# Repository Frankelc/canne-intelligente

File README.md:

# IFRI · Certification SEIoT · Projet 3

## Canne et lunettes intelligentes pour personnes non voyantes

Prototype d'aide expérimentale à la mobilité : détection d'obstacles à basse et à haute hauteur, messages vocaux locaux, transmission des événements vers un serveur MQTT sur VPS et alerte Telegram.

> **Sécurité :** ce prototype pédagogique ne remplace pas une canne blanche, un accompagnateur ni un dispositif médical certifié. Ne faites pas circuler une personne les yeux bandés sans accompagnateur et parcours sécurisé. La détection et l'audio locaux doivent rester fonctionnels sans Internet.

## 1. Objectifs

- Détecter les obstacles au sol et devant la personne avec trois capteurs ultrason sur la canne.
- Détecter certains obstacles à hauteur de tête avec un capteur ToF VL53L1X sur les lunettes.
- Fournir une indication vocale locale, sans attendre le réseau.
- Envoyer mesures, événements, état de connexion et demande SOS au VPS via MQTT.
- Afficher les événements sur un tableau de bord (par exemple Node-RED) et transmettre le SOS sur Telegram depuis le VPS.
- Concevoir deux cartes électroniques dans EasyEDA ou KiCad ; le prototype peut rester sur breadboard/plaque à pastilles.

## 2. Architecture

```text
VL53L1X sur lunettes
        │ I²C
ESP32-C3 des lunettes
        │ ESP-NOW : distance hauteur + état capteur
        ▼
ESP32 de la canne ◄── 3 ultrasons (gauche, centre, droite)
   │      │
   │      ├── DFPlayer Mini + écouteurs : guidage vocal local
   │      └── Bouton SOS
   │ Wi-Fi avec accès Internet (routeur ou partage de connexion)
   ▼
VPS : broker MQTT (Mosquitto) → Node-RED / tableau de bord
                            └→ service d'alerte → Bot API Telegram → proche
```

Le Wi-Fi de la canne sert à joindre le VPS. Les lunettes n'ont pas besoin d'Internet : elles envoient leurs mesures à la canne par ESP-NOW. L'ESP32 de la canne est le nœud passerelle. Il effectue la décision et les messages audio localement ; le VPS ne participe pas à la boucle critique de guidage.

### Attention au canal radio

ESP-NOW et la connexion Wi-Fi de la canne utilisent la radio 2,4 GHz. Quand la canne rejoint un point d'accès, elle fonctionne sur le canal de ce point d'accès. Les lunettes doivent alors émettre sur le même canal. Le canal du peer ESP-NOW peut être défini à `0` pour utiliser le canal courant, mais il faut valider le comportement avec les versions de cartes et bibliothèques retenues. Tester tôt : connexion Wi-Fi de la canne, puis réception ESP-NOW continue. Pour la démonstration, réserver un point d'accès stable (routeur ou téléphone) et éviter le changement automatique de canal.

## 3. Matériel

| Élément | Qté | Fonction |
|---|---:|---|
| ESP32 DevKit | 1 | Contrôleur principal de la canne, Wi-Fi/MQTT et décision |
| ESP32-C3 Super Mini (ou autre ESP32 compatible) | 1 | Contrôleur des lunettes et ESP-NOW |
| RCWL-1601 (ou HC-SR04) | 3 | Détection gauche, centre et droite |
| VL53L1X | 1 | Mesure ToF à hauteur de tête, bus I²C |
| DFPlayer Mini + micro-SD | 1 | Lecture des messages vocaux préenregistrés |
| Écouteurs filaires | 1 | Sortie audio locale |
| Bouton poussoir | 1 | Demande SOS par appui long |
| Batterie et alimentation adaptées | 2 jeux | Alimentation de la canne et des lunettes |
| Vibreur (optionnel) | 1 | Retour tactile local |
| Fils, connecteurs, plaque et boîtiers | selon besoin | Montage et intégration |

Les broches GPIO ne sont pas imposées ici : elles dépendent des révisions exactes des cartes et du câblage final. Les choisir dans les schémas des cartes, éviter les broches réservées au démarrage/flash, puis documenter la correspondance dans le code et le schéma électrique.

### Précautions électriques

- Les GPIO des ESP32 sont en logique 3,3 V et ne doivent pas recevoir 5 V.
- Avec un HC-SR04 alimenté en 5 V, la sortie ECHO peut être à 5 V : utiliser un diviseur résistif ou un convertisseur de niveau avant le GPIO. Vérifier la fiche technique du modèle réel.
- Ne pas alimenter moteurs, DFPlayer ou modules consommateurs directement depuis un GPIO. Prévoir alimentation adaptée, masse commune et étage de commande si nécessaire.
- Vérifier la plage d'alimentation exacte du breakout VL53L1X utilisé ; certains modules intègrent un régulateur et adaptation de niveau, d'autres non.
- Les trois ultrasons sont déclenchés l'un après l'autre pour réduire les interférences acoustiques.
- Protéger les batteries contre court-circuit et décharge excessive ; utiliser un chargeur/protecteur adapté à la chimie et au montage.

## 4. Fonctionnement local et logique

La canne échantillonne les trois distances au sol séquentiellement, reçoit la distance de hauteur par ESP-NOW, rejette les valeurs invalides, puis applique une logique à seuils. Valeurs initiales à calibrer dans la salle :

| Classe | Valeur initiale | Réaction indicative |
|---|---:|---|
| Danger | < 50 cm | Stop ou annonce prioritaire |
| Attention | 50 à 120 cm | Annonce d'obstacle / direction |
| Libre | > 120 cm | Pas d'annonce répétée |

Ces seuils sont des paramètres de démonstration, pas des valeurs de sécurité garanties. Un capteur seul ne décrit pas toute la géométrie d'un obstacle. Filtrer les mesures (par exemple médiane de trois échantillons), traiter les délais et valeurs hors plage comme des erreurs, et limiter la répétition des mêmes annonces. La détection en hauteur peut être prioritaire dans l'audio. Garder les annonces brèves afin de préserver l'audition des sons ambiants.

### Messages audio suggérés

| Fichier | Message |
|---|---|
| `0001.mp3` | Obstacle à gauche |
| `0002.mp3` | Obstacle à droite |
| `0003.mp3` | Obstacle devant, allez à gauche |
| `0004.mp3` | Obstacle devant, allez à droite |
| `0005.mp3` | Stop, obstacle |
| `0006.mp3` | Attention, obstacle en hauteur |
| `0007.mp3` | Continuez tout droit |
| `0008.mp3` | Alerte envoyée |
| `0009.mp3` | Système prêt |

Nommer les fichiers selon les exigences du DFPlayer et tester d'abord la carte SD et la sortie audio séparément.

## 5. MQTT et données

### Topologie

- Le VPS héberge Mosquitto, accessible depuis Internet sur le port MQTT choisi.
- L'ESP32 de la canne se connecte au réseau Wi-Fi avec accès Internet, puis au broker MQTT du VPS.
- Node-RED (sur le VPS ou une machine autorisée) s'abonne aux sujets pour afficher valeurs et événements.
- Un service d'alerte (flow Node-RED ou petit programme) s'abonne au sujet SOS et appelle Telegram.
- Le projet reste utile hors ligne : les mesures, décisions, vibrations et voix sont locales. Les données distantes sont opportunistes.

### Sujets proposés

Préfixe du projet : `ifri/seiot/projet3/canne01/`.

| Sujet | Exemple de payload | QoS / rétention conseillée |
|---|---|---|
| `.../telemetry` | JSON avec distances, batterie, horodatage/uptime | QoS 0, non retenu (mesures fréquentes) |
| `.../event` | `{"type":"obstacle","zone":"gauche","distance_cm":42}` | QoS 1, non retenu |
| `.../status` | `{"wifi":true,"espnow":true,"uptime_s":120}` | QoS 1, retained |
| `.../sos` | `{"event":"SOS","device":"canne01","uptime_s":1234}` | QoS 1, non retenu |
| `.../availability` | `online` ou `offline` (Last Will) | QoS 1, retained |

Exemple de télémétrie :

```json
{
  "device": "canne01",
  "left_cm": 145,
  "center_cm": 48,
  "right_cm": 132,
  "head_cm": 76,
  "battery_pct": 82,
  "uptime_s": 3600
}
```

Publier la télémétrie à faible fréquence (par exemple une fois par seconde) et publier immédiatement les événements utiles. Pour le SOS, utiliser QoS 1, vérifier la connexion et afficher une confirmation locale uniquement quand l'événement a été publié/confirmé selon le mécanisme choisi. QoS 1 signifie « au moins une fois » : prévoir un `event_id` et une déduplication côté serveur pour éviter plusieurs notifications Telegram lors d'une reconnexion.

Ne pas publier chaque mesure de capteur toutes les 100 ms : cela surcharge le réseau et le tableau de bord sans apporter d'avantage à la démonstration.

### Sécurité du broker

- Créer un compte MQTT dédié à l'appareil, avec un mot de passe fort et des droits limités aux sujets de ce projet.
- Ne pas laisser Mosquitto accessible en anonyme sur Internet.
- Préférer MQTT sur TLS (port usuel 8883) avec certificat valide. Pour un prototype sur réseau de confiance, si TLS est temporairement omis, documenter cette limite et restreindre l'accès réseau par pare-feu ; ne jamais transmettre de secret Telegram à l'ESP32.
- Stocker les identifiants Wi-Fi/MQTT hors du dépôt public (fichier local non versionné ou secrets de compilation). Ne pas afficher les mots de passe ou jetons dans les slides/captures.
- Utiliser un pare-feu VPS : n'exposer que les ports nécessaires. L'interface Node-RED doit être protégée et ne pas être publiée sans authentification.

## 6. Alerte Telegram via le VPS

Le VPS, et non l'ESP32, détient le jeton du bot. Le service serveur s'abonne à `.../sos`, valide le payload et l'identifiant de l'appareil, applique une temporisation anti-doublon, puis appelle la méthode `sendMessage` de la Bot API Telegram avec le `chat_id` du proche. Il faut créer le bot avec BotFather et le destinataire doit avoir démarré le bot pour recevoir ses messages.

```text
Appui long SOS → ESP32 canne publie MQTT → VPS reçoit SOS
              → service vérifie/déduplique → Telegram avertit le proche
```

Message possible : `SOS — demande d'assistance depuis la canne canne01. Heure/état : ...`.

Configurer le jeton et le `chat_id` dans des variables d'environnement ou un fichier de secrets protégé côté VPS. Ne pas les écrire dans ce README ni dans le firmware. L'accusé local « alerte envoyée » ne doit pas laisser croire qu'un proche l'a reçue : distinguer « SOS transmis au VPS » et « confirmation Telegram » si un retour serveur est implémenté.

## 7. Déploiement du VPS (vue d'ensemble)

1. Installer un système Linux maintenu et mettre à jour les paquets.
2. Installer Mosquitto et ses outils clients, créer un utilisateur dédié, activer l'authentification et les ACL.
3. Configurer le pare-feu pour n'autoriser que les ports nécessaires ; activer TLS si possible.
4. Tester la publication et l'abonnement MQTT depuis un poste de développement avant de connecter la canne.
5. Installer Node-RED (ou un service serveur léger) et protéger son accès.
6. Créer le flow/service : abonnement MQTT, affichage de télémétrie, traitement SOS, appel Telegram et journalisation minimale.
7. Tester un SOS avec un événement simulé avant le bouton physique.
8. Redémarrer le VPS et vérifier que Mosquitto et le service d'alerte repartent automatiquement.

Les détails de commandes dépendent de la distribution et de la configuration du VPS ; ne pas copier une configuration sans vérifier les chemins, versions et règles de pare-feu de la machine utilisée.

## 8. Programme des deux ESP32

### ESP32-C3 des lunettes

1. Initialiser le VL53L1X sur I²C et vérifier la présence du capteur.
2. Lire la distance, marquer les erreurs/timeout et éviter d'envoyer une valeur périmée comme une mesure valide.
3. Initialiser ESP-NOW, cibler l'adresse MAC de la canne et envoyer un paquet compact, par exemple `{sequence, distance_mm, valid, battery_mv}`.
4. Envoyer périodiquement (ex. 5 à 10 fois/s) ; le rythme exact doit être mesuré et ne pas saturer le traitement.
5. Signaler localement une perte de liaison si elle est détectable.

### ESP32 de la canne

1. Initialiser les capteurs, le DFPlayer, le bouton SOS et les fonctions locales.
2. Connecter le Wi-Fi, obtenir l'état et le canal, puis démarrer ESP-NOW avec le canal compatible et enregistrer le peer des lunettes.
3. Recevoir les paquets ESP-NOW sans bloquer la boucle audio/capteurs ; conserver la date de dernière réception.
4. Déclencher les ultrasons en séquence, filtrer, décider, et commander audio/vibreur.
5. Gérer MQTT de manière non bloquante : reconnexion temporisée, Last Will `offline`, publication périodique et événements.
6. Détecter l'appui long SOS, publier un événement unique avec identifiant et permettre une nouvelle tentative si le réseau est indisponible.
7. Continuer sans Wi-Fi : pas de blocage durable de la logique de sécurité locale.

Ne pas faire de requête réseau bloquante dans les callbacks ESP-NOW ni dans la boucle de détection. Utiliser des temporisations avec `millis()` ou des tâches séparées. Garder les paquets réseau petits et versionnés (`"v":1`).

## 9. Plan de réalisation sur cinq jours

| Jour | Résultat attendu |
|---|---|
| J1 | Tester séparément ESP32, un ultrason, VL53L1X, DFPlayer, connexion MQTT depuis un ordinateur et broker VPS. Créer le bot Telegram et valider un message depuis un script serveur. |
| J2 | Réaliser la détection canne locale : trois ultrasons séquentiels, filtrage, décisions, messages vocaux. Établir les sujets/payloads MQTT. |
| J3 | Faire communiquer lunettes→canne par ESP-NOW, y compris pendant la connexion Wi-Fi/MQTT de la canne. Publier télémétrie et événements ; traiter SOS vers Telegram. |
| J4 | Intégrer mécaniquement et électriquement, calibrer, mesurer portée ESP-NOW, délai, précision et autonomie. Terminer les schémas/PCB et tester la perte réseau. |
| J5 | Répéter le parcours accompagné, vérifier toutes les batteries, enregistrer une vidéo de secours, préparer le tableau de bord et l'exposé. |

**Priorité si le temps manque :** sécurité et guidage local → ESP-NOW → MQTT télémétrie → alerte SOS Telegram → tableau de bord avancé → routage PCB complet.

## 10. Tests et critères de validation

- VL53L1X : comparer distances mesurées/réelles à plusieurs points et noter les cas d'échec.
- Ultrasons : tester séparément plusieurs distances, matériaux et angles ; vérifier qu'ils ne sont pas déclenchés simultanément.
- ESP-NOW : vérifier réception répétée de la distance de hauteur pendant que la canne est connectée au Wi-Fi et au broker.
- Audio : contrôler la bonne annonce, l'anti-répétition, la priorité hauteur et la disponibilité du son hors ligne.
- MQTT : tester télémétrie, événement, reconnexion, Last Will et droits d'accès.
- Telegram : envoyer un message simulé, puis tester le bouton SOS et la déduplication.
- Panne réseau : couper le Wi-Fi/Internet ; le système local doit continuer et la reconnexion ne doit pas bloquer le guidage.
- Énergie : mesurer la tension et l'autonomie réelle ; afficher une estimation de batterie seulement si elle est calibrée.
- Démo : parcours dégagé, accompagnateur à portée immédiate, vitesse lente, arrêt possible et vidéo de secours.

Consigner les résultats réellement observés. Ne pas présenter une valeur cible ou une simulation comme une mesure effectuée.

## 11. Répartition des rôles

- **R1 — Électronique/PCB :** câblage, alimentation, schémas, ERC/DRC, cartes canne et lunettes.
- **R2 — Firmware/IoT :** deux firmwares, ESP-NOW, logique, MQTT, VPS et alerte Telegram.
- **R3 — Mécanique/tests :** support des capteurs, montage, sécurité du parcours, mesures et calibration.
- **R4 — Documentation/exposé :** état de l'art, architecture, résultats, slides et vidéo de secours.

## 12. Risques et plans de repli

| Risque | Réponse prévue |
|---|---|
| Pas d'Internet ou VPS injoignable | Guidage/audio local maintenu ; tableau de bord et Telegram indisponibles, événements éventuellement mis en tampon. |
| Canal Wi-Fi changeant | Fixer le canal du point d'accès si possible ; resynchroniser/tester ESP-NOW après connexion. Démo locale sans lunettes en dernier recours. |
| Telegram indisponible | MQTT et tableau de bord continuent ; journaliser l'échec et réessayer avec temporisation. |
| Faux positifs ou mesure invalide | Filtrer, rejeter les timeouts, calibrer ; présenter les limites et ne pas dépendre du capteur seul. |
| Capteur ou module manquant | Adapter le prototype, documenter le remplacement et distinguer clairement matériel réel et conception. |
| Retard PCB | Présenter schéma, ERC/DRC disponibles et vue 3D ; prototype sur plaque à pastilles selon le temps. |
| Démo en direct échoue | Vidéo de secours, démonstration statique des messages MQTT et explication du mode dégradé. |

## 13. Livrables

- Firmware des lunettes et de la canne, avec configuration secrète exclue du dépôt.
- Schéma électrique complet des deux cartes, ERC, routage, DRC, vues 3D et Gerber/BOM si terminés.
- Configuration du broker (sans secrets), sujets MQTT et exemples de payloads.
- Flow Node-RED ou service d'alerte Telegram, sans jeton ni identifiant privé dans les fichiers livrés.
- Tableau de mesures, photos du montage, captures du tableau de bord et vidéo de démonstration.
- Présentation : besoin, architecture, fonctionnement, résultats mesurés, limites, risques et améliorations.

## 14. Améliorations futures

Écouteurs à conduction osseuse, meilleure gestion de batterie, GPS extérieur, capteurs redondants, diagnostic de liaison, mise à jour logicielle sécurisée, journal d'événements fiable, et étude utilisateur encadrée avant tout usage réel.

---

**Projet de formation IFRI · Certification SEIoT · Document de travail du groupe**

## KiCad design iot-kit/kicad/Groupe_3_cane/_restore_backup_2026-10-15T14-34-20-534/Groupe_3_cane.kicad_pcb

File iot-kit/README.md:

# Kit IoT : canne, lunettes, VPS et Telegram

Partie IoT du projet 3 (IFRI, certification SEIoT) : canne et lunettes intelligentes pour personnes non voyantes.

Chemin des données dans l'architecture finale, validée sur le matériel (SOS Telegram compris) :

```text
Casque Bluetooth ◄── Canne (ESP32) ◄──ESP-NOW──► Lunettes (ESP32, passerelle) ──MQTT/TLS 8883──► VPS ──► Telegram
   voix A2DP        3 ultrasons, décision,        capteur tête + Wi-Fi                          Mosquitto, relais Telegram,
                    voix, bouton SOS              publie tout sur le VPS                         tableau de bord HTTPS 8443
```

- **La canne n'a pas d'Internet.** Son ESP32 n'a pas assez de mémoire pour le Bluetooth audio et une connexion TLS en même temps (13 Ko libres avant la répartition, 73 Ko après). Elle mesure, décide et parle dans le casque Bluetooth, même sans réseau.
- **Les lunettes servent de passerelle.** Elles reçoivent de la canne les distances, les annonces et les SOS (ESP-NOW), les publient sur le VPS, et renvoient à la canne l'état du VPS et la confirmation des SOS.
- **Le VPS** reçoit tout en MQTT/TLS, prévient le proche sur Telegram et affiche le tableau de bord.

Les raisons de ces choix sont détaillées dans [CHOIX_IOT.md](CHOIX_IOT.md).

## Contenu

| Dossier | Rôle |
|---|---|
| `firmware/canne/` | Canne : 3 HC-SR04, décision, voix Bluetooth (clips en mémoire flash), bouton SOS, ESP-NOW |
| `firmware/lunettes/` | Lunettes : HC-SR04 tête, ESP-NOW, passerelle Wi-Fi + MQTT/TLS (`iot.cpp`) |
| `dashboard/` | Tableau de bord Flask (`dashboard.py`) et sa page (`index.html`) |
| `telegram-bridge/` | Relais SOS vers Telegram (`bridge.py`), avec accusé de réception |
| `vps-user/` | **Installation actuelle** sur le VPS partagé, sans `sudo` ni Docker |
| `mosquitto/` | Configuration du courtier MQTT |
| `deploy/`, `docker-compose.yml`, `caddy/` | Variante Docker pour un VPS dont on est administrateur (non utilisée) |
| `Code/` | Premiers programmes de l'équipe, gardés pour mémoire (obsolètes) |

## Installation actuelle : VPS partagé (`vps-user/`)

Le VPS du projet (185.215.164.23) est partagé : les ports 80 et 443 appartiennent à un autre service, et le compte `groupe3` n'a ni `sudo` ni Docker. `vps-user/install.sh` installe donc tout dans `~/iot-canne`, sans rien modifier d'autre sur la machine :

- Mosquitto est extrait des paquets Ubuntu (sans installation système) ; Python tourne dans `~/iot-canne/venv` ;
- MQTT/TLS sur le port **8883**, tableau de bord HTTPS avec mot de passe sur le port **8443** ;
- certificats signés par une autorité propre au projet (`certs/ca.crt`), connue de l'ESP32 des lunettes ; le navigateur affiche un avertissement la première fois ;
- redémarrage automatique : deux lignes `# iot-canne` dans la crontab de `groupe3` ;
- à la fin, `~/iot-canne/config-mqtt.h` contient le bloc MQTT à recopier dans `firmware/lunettes/config.h`.

Commandes sur le VPS :

```sh
bash ~/iot-canne/run.sh status          # état des 3 services
bash ~/iot-canne/run.sh restart
bash ~/iot-canne/test-sos.sh            # SOS de test vers Telegram, sans ESP32
tail -f ~/iot-canne/logs/telegram.log   # journaux : mosquitto, telegram, dashboard
grep DASHBOARD_PASSWORD ~/iot-canne/.env
```

### Mettre à jour le tableau de bord ou le relais

Depuis le PC (PowerShell), dans le dossier `iot-kit` :

```sh
scp telegram-bridge/bridge.py dashboard/dashboard.py dashboard/index.html groupe3@185.215.164.23:~/iot-canne/app/
ssh groupe3@185.215.164.23 "bash ~/iot-canne/run.sh restart"
```

Si `vps-user/*` a changé, copier aussi ces fichiers dans `~/iot-canne/` puis lancer `bash ~/iot-canne/install.sh` (relançable : mots de passe et certificats existants conservés).

## Firmwares ESP32

Arduino IDE, cœur **Arduino-ESP32 3.x**, carte **ESP32 Dev Module**, moniteur série à 115200 bauds. Les fichiers `config.h` contiennent des secrets : ils ne sont jamais publiés (voir `.gitignore`). On les crée en copiant `config.example.h`.

### Canne : `firmware/canne/`

- Bibliothèque **ESP32-A2DP** (pschatzmann, depuis GitHub).
- **Outils → Partition Scheme → « Huge APP (3MB No OTA/1MB SPIFFS) »** : le Bluetooth et les messages vocaux dépassent la taille par défaut.
- `config.h` : `WIFI_SSID` (le même nom que dans les lunettes ; la canne ne s'y connecte pas, elle s'en sert pour se caler sur le même canal radio) et `BT_HEADSET_NAME` (nom **exact** du casque, majuscules ignorées : la canne ne se connecte à aucun autre appareil ; laisser vide pour lister les appareils trouvés dans le moniteur série). Casque du projet : « Amis Hi580MAX ».
- Câblage : gauche Trig 13 / Echo 34, centre Trig 14 / Echo 35, droite Trig 27 / Echo 32 (Echo par pont diviseur), bouton SOS entre GPIO 25 et GND.

### Lunettes : `firmware/lunettes/`

- Bibliothèque **PubSubClient**.
- `config.h` : `WIFI_SSID` / `WIFI_PASSWORD` (partage de connexion du téléphone), puis le bloc MQTT généré par `install.sh` sur le VPS (`config-mqtt.h`). `BATTERY_ADC_PIN` reste à `-1` tant que le pont diviseur de la batterie n'est pas câblé.
- Câblage : Trig 13, Echo 34 par pont diviseur (1 kΩ / 2 kΩ), 3 piles AA sur VIN.
- Moniteur série attendu : `[iot] MQTT connecté au VPS (TLS)`.

`protocole.h` décrit les paquets ESP-NOW. **Il doit être identique dans les deux dossiers.**

**Règle radio.** Les lunettes se connectent au partage de connexion ; la canne cherche le même réseau et se place sur son canal (canal 1 s'il est absent). Il faut donc **activer le partage de connexion avant d'allumer les deux cartes**, et ne pas le couper pendant la démo. Si le partage redémarre sur un autre canal, redémarrer les deux cartes.

### Guidage vocal (canne)

| Situation | Seuil | Annonce |
|---|---|---|
| Obstacle à hauteur de tête (lunettes) | < 100 cm | « Attention, obstacle en hauteur », prioritaire |
| Obstacle devant | < 120 cm | « Obstacle devant, allez à gauche/droite » ou « Stop, obstacle », répété toutes les 4 s |
| Obstacle sur le côté | < 60 cm | « Obstacle à gauche/droite », dit une fois |
| Fin d'un obstacle devant | | « Continuez tout droit », une fois |

Un obstacle n'est considéré comme parti qu'au-dessus de son seuil + 20 cm : cette marge évite les annonces qui « clignotent » quand la distance hésite autour du seuil.

## Sujets MQTT

Préfixe : `ifri/seiot/projet3/canne01`. Toutes les cartes publient **via les lunettes**.

| Sujet | Émetteur | Contenu | QoS |
|---|---|---|---:|
| `.../telemetry` | lunettes | Mesures, chaque seconde | 0 |
| `.../event` | lunettes | Message vocal joué par la canne | 0 |
| `.../sos` | lunettes | SOS, répété toutes les 5 s jusqu'à l'accusé | 0 |
| `.../sos/ack` | relais | Accusé : `envoye` ou `deja_signale` | 1 |
| `.../availability` | lunettes | `online` / `offline` de la **passerelle** (retenu, Last Will) | 1 |

Télémétrie :

```json
{"v":1,"device":"canne01","left_cm":85,"center_cm":null,"right_cm":140,"head_cm":null,
 "battery_pct":null,"espnow":true,"headset":true,"rssi":-61,"sos_pending":false,"uptime_s":42}
```

- distances : `null` signifie « rien détecté dans la portée » ; gauche, centre et droite sont aussi à `null` quand la canne n'est pas joignable ;
- `espnow` : la canne est joignable par les lunettes ; `headset` : le casque Bluetooth de la canne est connecté ;
- `rssi`, `uptime_s` et `battery_pct` sont ceux **des lunettes**.

Annonce : `{"v":1,"type":"annonce","mp3":6,"message":"Attention, obstacle en hauteur"}` (`mp3` est le numéro du message, de 1 à 10).

SOS : `{"v":1,"event":"SOS","event_id":"a3f09c1e-7","device":"canne01","age_s":0,"attempt":1,"glasses":true}`. L'identifiant est formé de 8 caractères hexadécimaux, d'un tiret et du numéro de SOS choisi par la canne.

**Fiabilité du SOS.** Appui long (1,5 s) sur le bouton : la canne envoie un numéro de SOS aux lunettes, qui le publient toutes les 5 s (30 min au plus) jusqu'à l'accusé. PubSubClient ne publie qu'en QoS 0 : la fiabilité vient de cet accusé applicatif. Le relais n'envoie Telegram qu'une fois par `event_id` (liste gardée sur disque, même après un redémarrage) et ne publie l'accusé qu'une fois le message accepté par Telegram. Les lunettes transmettent alors la confirmation à la canne, qui dit « Alerte envoyée ». Sans confirmation au bout de 20 s, elle dit « Alerte non envoyée » et l'envoi continue en arrière-plan.

## Tableau de bord

`https://185.215.164.23:8443`, protégé par mot de passe (`DASHBOARD_USER` / `DASHBOARD_PASSWORD` dans `~/iot-canne/.env`). Il ne fait que refléter l'état : le guidage se fait dans la canne, sans Internet.

- **Chaîne de liaison** : casque Bluetooth, canne (`espnow`), passerelle (`availability`), VPS et Telegram, chacun avec son état ; en dessous, batterie et Wi-Fi des lunettes, temps de marche de la passerelle, SOS en cours.
- **Radar de la canne** : vue de dessus des 3 ultrasons avec les vrais seuils (côtés 60 cm, devant 120 cm) et la marge de 20 cm. Chaque état a une couleur, une forme et un mot (« Annoncé », « Marge », « Hors seuil », « Libre »).
- **Deux hauteurs couvertes** : vue de profil, tête (lunettes, seuil 100 cm) et sol devant (canne, seuil 120 cm).
- **Ce qu'entend la personne** : dernier message joué dans le casque. Le bouton « Voix » le lit aussi à voix haute sur l'ordinateur (à activer d'un clic avant la démo).
- **SOS** : alerte plein écran, suivie jusqu'à « Telegram envoyé ».
- **Mode projecteur** : bouton « Projecteur » (ou `?theme=clair`) pour un fond clair et un texte agrandi, plus lisibles au vidéoprojecteur. Le choix est mémorisé.
- **Mode simulation** : `?demo=1` rejoue en boucle un parcours d'une minute au format réel (obstacles, casque déconnecté, passerelle hors ligne, SOS). `&t=25` démarre à la 25e seconde. Un bandeau bleu signale la simulation : ne pas l'utiliser pendant la vraie démo.

Le contrat de `/api/state` est stable : `telemetry`, `telemetry_at`, `availability`, `events`, `stats`, `now`.

## Dépannage rapide

- **Passerelle hors ligne** au tableau de bord : vérifier le partage de connexion et le moniteur série des lunettes (`MQTT échec`, état TLS, mémoire libre).
- **Canne injoignable** alors que la passerelle est en ligne : canne éteinte, hors de portée, ou sur un autre canal radio (redémarrer les deux cartes après avoir activé le partage).
- **Casque déconnecté** : vérifier `BT_HEADSET_NAME` et que le casque n'est pas connecté à un autre appareil.
- **Pas de Telegram** : vérifier que le bot a reçu `/start`, le jeton et le chat ID dans `.env`, puis `logs/telegram.log`.
- **Sans Internet** : la détection et la voix continuent ; seuls le tableau de bord et l'alerte à distance sont indisponibles.

## Variante Docker (VPS administré)

Pour un VPS dont on est administrateur, `deploy/deploy.sh` installe la même chaîne avec Docker, un certificat Let's Encrypt (domaine requis) et Caddy devant le tableau de bord. Elle n'est pas utilisée sur le VPS actuel. Le bloc MQTT généré (`deploy/config-mqtt.h`) se recopie aussi dans `firmware/lunettes/config.h`.

## Création du bot Telegram

1. Dans Telegram, créer un bot avec `@BotFather` et copier son jeton dans `.env` sur le VPS.
2. Ouvrir une conversation avec ce bot et envoyer `/start`.
3. Renseigner l'identifiant de chat dans `TELEGRAM_CHAT_ID` (plusieurs possibles, séparés par des virgules).
4. Redémarrer : `bash ~/iot-canne/run.sh restart`.
5. Ne jamais mettre le jeton dans un firmware, un document, Git ou une capture d'écran.

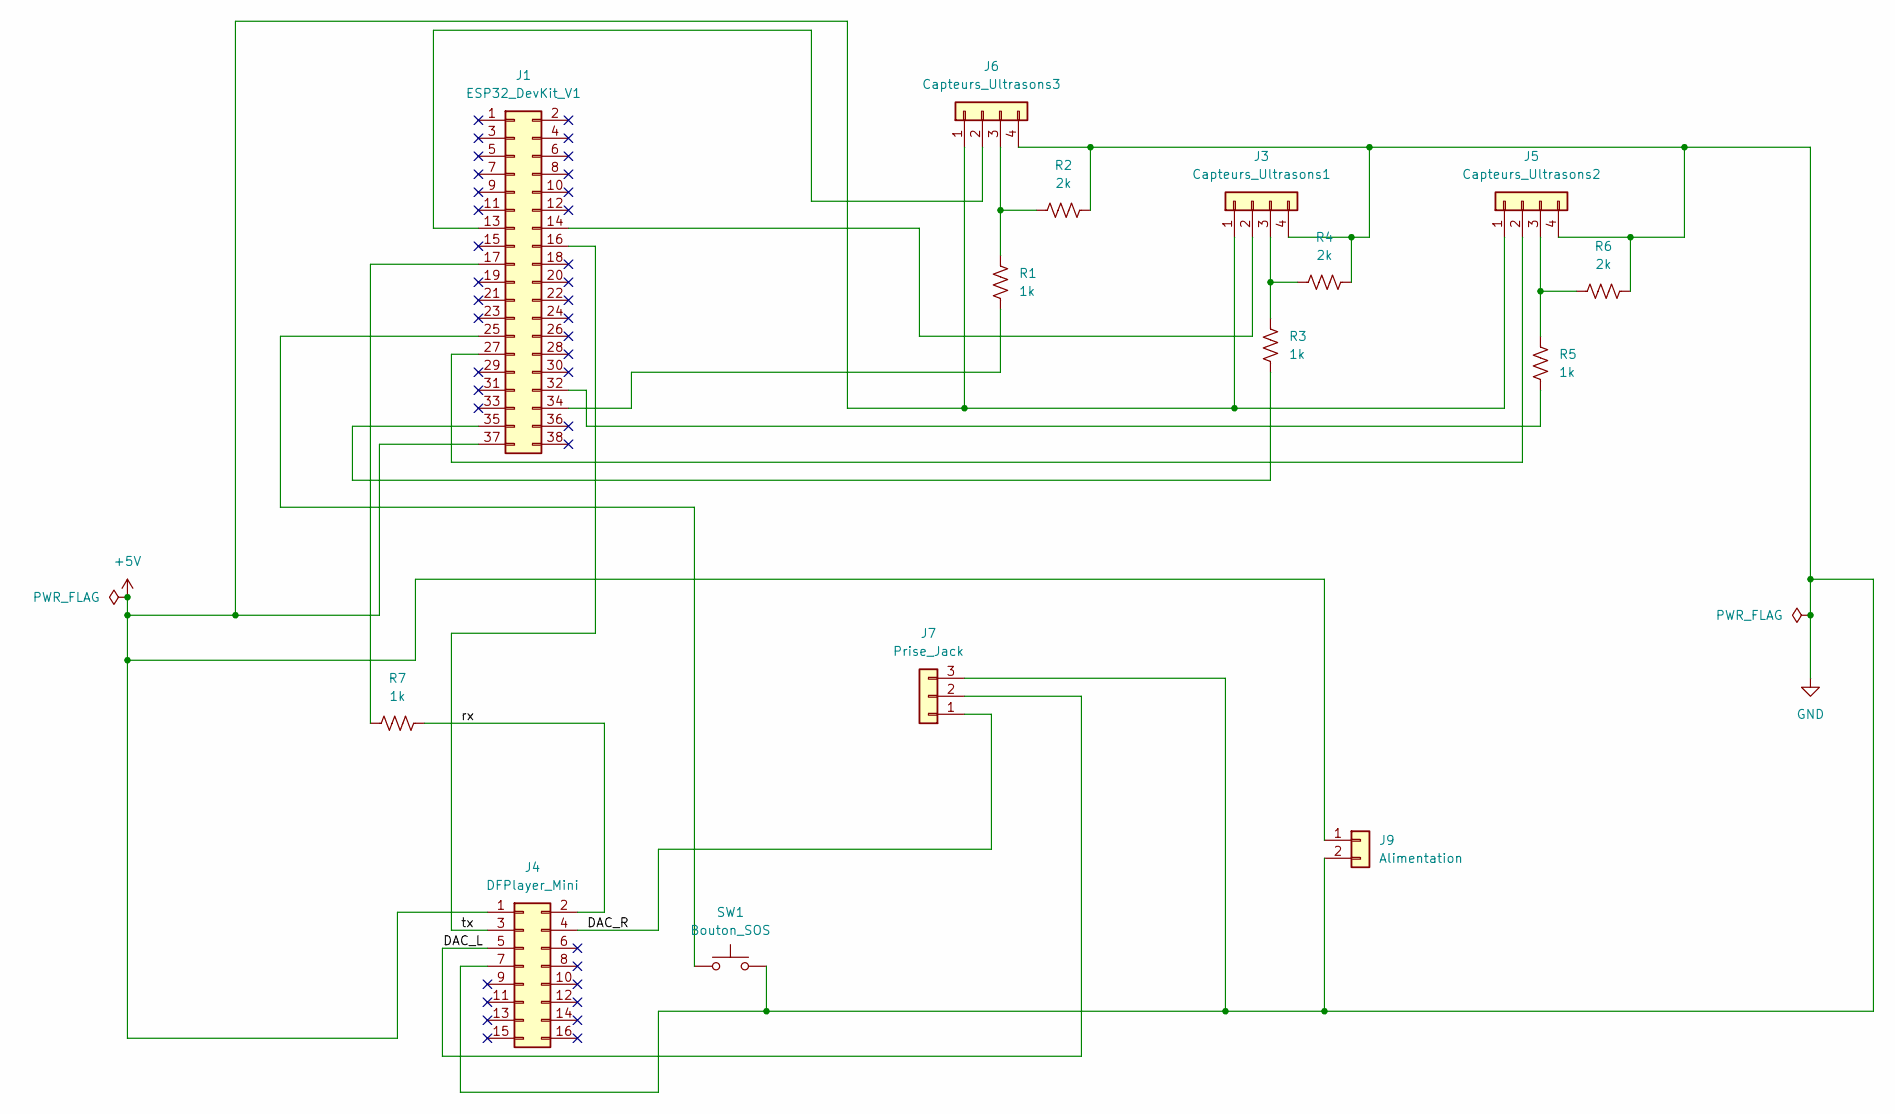
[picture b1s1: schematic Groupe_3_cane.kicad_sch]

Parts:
J1: ESP32_DevKit_V1; PinSocket_2x19_P2.54mm_Vertical
J3: Capteurs_Ultrasons1; PinSocket_1x04_P2.54mm_Vertical
J4: DFPlayer_Mini; PinSocket_2x08_P2.54mm_Vertical
J5: Capteurs_Ultrasons2; PinSocket_1x04_P2.54mm_Vertical
J6: Capteurs_Ultrasons3; PinSocket_1x04_P2.54mm_Vertical
J7: Prise_Jack; PinSocket_1x03_P2.54mm_Vertical
J9: Alimentation; PinSocket_1x02_P2.54mm_Vertical
R1, R3, R5, R7: 1k; R_Axial_DIN0207_L6.3mm_D2.5mm_P10.16mm_Horizontal
R2, R4, R6: 2k; R_Axial_DIN0207_L6.3mm_D2.5mm_P10.16mm_Horizontal
SW1: Bouton_SOS; SW_PUSH_6mm

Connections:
+5V: J1.37, J3.1, J4.1, J5.1, J6.1, J9.1
/DAC_L: J4.5, J7.2
/DAC_R: J4.4, J7.1
/rx: J4.2, R7.2
/tx: J1.16, J4.3
GND: J3.4, J4.7, J5.4, J6.4, J7.3, J9.2, R2.2, R4.2, R6.2, SW1.2
unnamed: J1.13, J6.2
unnamed: J1.14, J3.2
unnamed: J1.17, R7.1
unnamed: J1.25, SW1.1
unnamed: J1.27, J5.2
unnamed: J1.32, R5.2
unnamed: J1.34, R1.2
unnamed: J1.35, R3.2
unnamed: J3.3, R3.1, R4.1
unnamed: J5.3, R5.1, R6.1
unnamed: J6.3, R1.1, R2.1

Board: 2 copper layers, 15 parts (0 on the bottom side), 17 nets, no tracks yet.

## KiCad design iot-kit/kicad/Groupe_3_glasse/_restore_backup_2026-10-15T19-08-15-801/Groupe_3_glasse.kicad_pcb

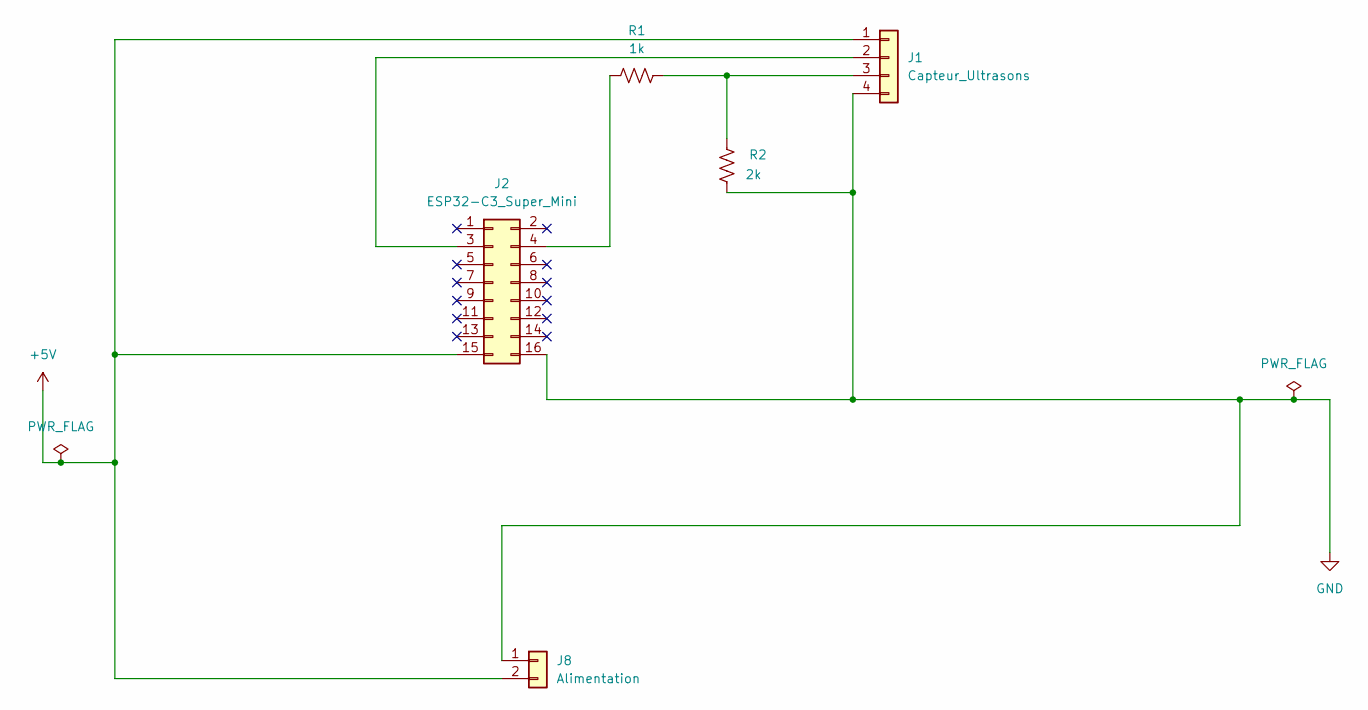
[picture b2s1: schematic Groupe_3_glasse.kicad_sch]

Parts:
J1: Capteur_Ultrasons; PinSocket_1x04_P2.54mm_Vertical
J2: ESP32-C3_Super_Mini; PinSocket_2x08_P2.54mm_Vertical
J8: Alimentation; PinSocket_1x02_P2.54mm_Vertical
R1: 1k; R_Axial_DIN0207_L6.3mm_D2.5mm_P10.16mm_Horizontal
R2: 2k; R_Axial_DIN0207_L6.3mm_D2.5mm_P10.16mm_Horizontal

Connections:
+5V: J1.1, J2.15, J8.2
GND: J1.4, J2.16, J8.1, R2.2
unnamed: J1.2, J2.3
unnamed: J1.3, R1.2, R2.1
unnamed: J2.4, R1.1

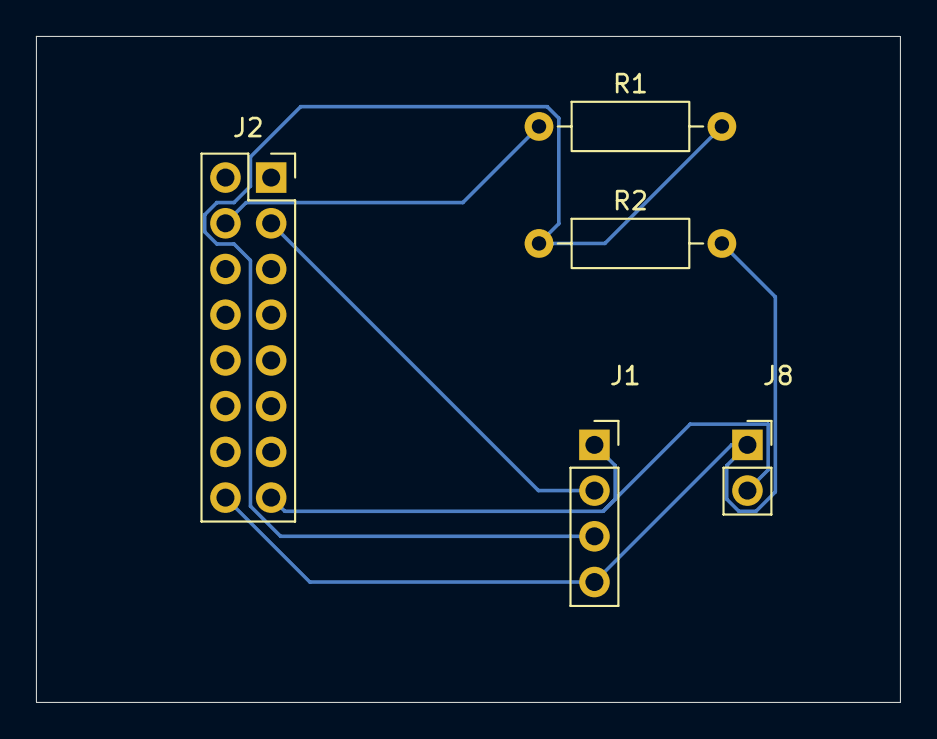
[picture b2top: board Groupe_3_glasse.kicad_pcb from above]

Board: 2 copper layers, 48.0 x 37.0 mm, 5 parts (0 on the bottom side), 5 nets.
